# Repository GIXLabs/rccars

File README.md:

# Purpose

The following tutorial will get you up and running to build an RC car with the provided materials. All of the soldering is already done and the most of the code is flashed onto the brain board. It will be your responsibility to use the tools provided to you in your orientation bag along with the tools available in the Prototyping Lab to design and build a chassis for your car.

### Bill of Materials

# Electronics Assembly

1. Collect the above components from the Prototyping Lab staff.

1. Attach the components to the individual boards. AAA battery pack to brain board (only goes in one way). Bluetooth module to Bluetooth board (RCA, not RCM). Motors to motor board (needs a screwdriver and wires may need to be switched later).

1. Stack the boards together with the brain at the bottom and Bluetooth at the top. Make sure to align them properly (see image).

1. Try placing 3 AAA batteries in their holder and turn it on. If you've assembled everything correctly, the blue and red lights on the underside of the Bluetooth module should start blinking.

# Flashing Code

1. The code for the brain board is written in CircuitPython, which means you will not need to download any software to edit and manipulate the code. 
1. Download the RC Car code from [here](src/python/code.py). Make sure it is named `code.py`.

1. Using a micro USB cable, connect the brain board to your computer (you do not need to disconnect the other boards). Your computer should now have a new USB drive available named `CIRCUITPY` where the code is stored.
1. Click and drag `code.py` onto `CIRCUITPY`, replacing the file that is on the drive.
1. Your code should now be running on the brain board. If you would like to edit this code, just open `code.py` in any text editor (TextEdit and NotePad are fine). The new code will run whenever you save.
    1. Editing code this way does not give you access to any debugging outputs, so you may want to edit using [Mu](https://codewith.mu/en/download) or [Thonny](https://thonny.org/) so you can read any `print()` statements you add to the code.
    1. The max speed of the default code is slow, which you may want to change if you want to win the race.
    1. Python uses spacing in a particular way, so you may need to match the indendation of lines.
    1. For more details on how the code works see [here.](src/README.md)

# Connecting via Remote
1. Place the Bluetooth module marked `RCM` in the remote. It should only fit one way.

1. Plug in the 9V batteries on both your remote and turn on the AAA batteries on your car.

1. The lights on the Bluetooth dongles (HC-05) will stop blinking when they have successfully paired.

1. If it fails to pair, try power cycling the car ands the remote.

# Make your Chassis
1. Design and build the body of the RC car, you are welcome to use the materials provided in the Prototyping Lab from cardboard to wood. Make sure it holds everything! We've produced a tutorial if you'd like to start with a lasered template [here](lasering.md).

1. Attach the gear motors to the body of the RC car that you have designed/built and assemble the tires. Depending on how you attach the motors, you may have to change some wires to get it to move forward (instructions below).

# Debugging Motors
If you have been able to connect to your RC car, but it is going the wrong direction, you may need to swap the motor wires.
- If your car is going backward when it should be going forward - Swap the red and black wires on both motors.
- If your car is going left when it should be going right or right when it should be going left - Swap which side of the motor driver your motors are wired to.
- For other problems, ask a member of the Prototyping Lab staff.

### Congratulations you are now connected to the RC car! Happy racing! 🏁🏎

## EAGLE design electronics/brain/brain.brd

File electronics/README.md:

# Purpose
This is where any information about the electronics will go. The Eagle files (.sch and .brd) will be in a subdirectory).

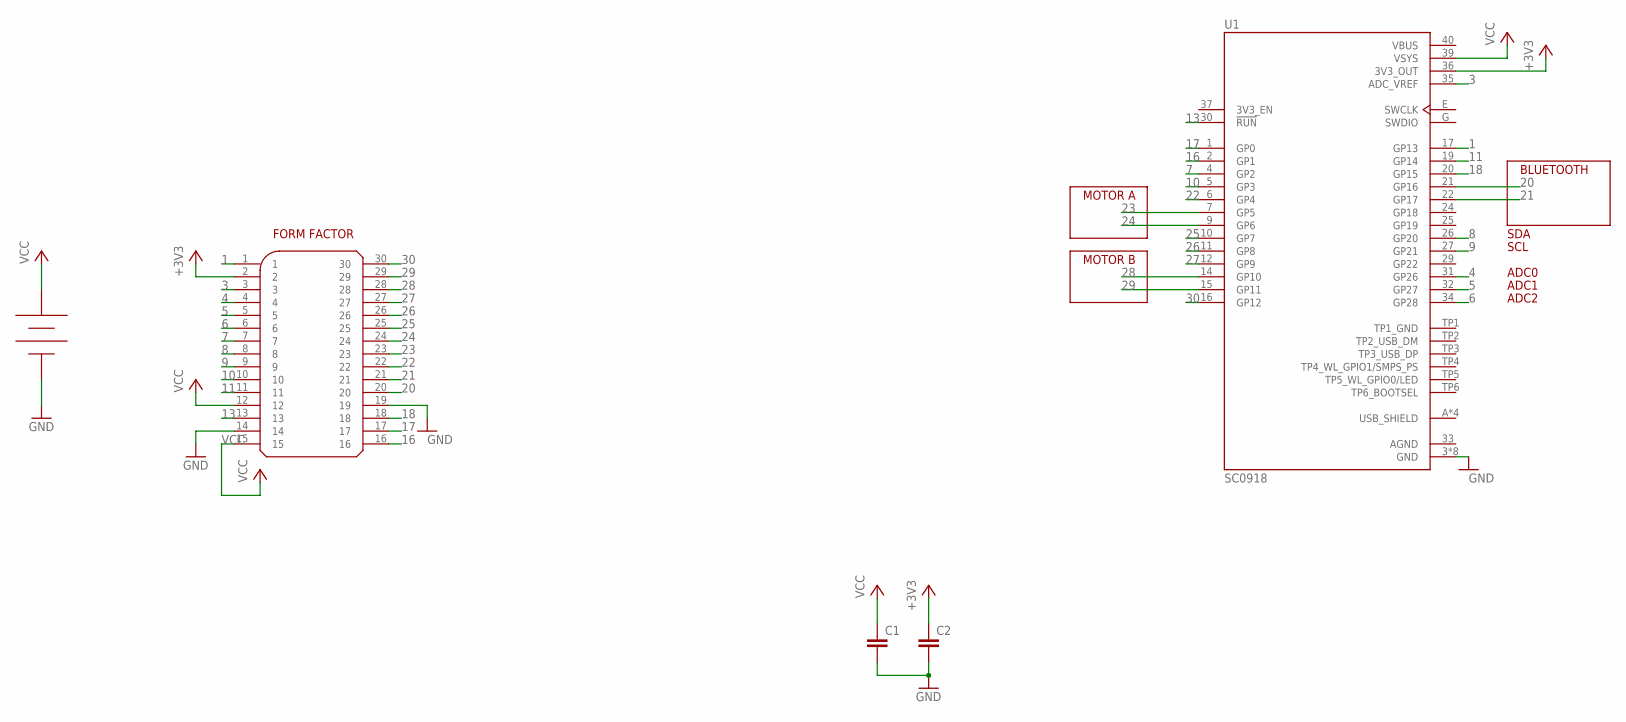
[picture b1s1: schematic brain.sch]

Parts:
C1, C2: C-EU050-025X075; C050-025X075
U1: SC0918; MODULE_SC0918
U$4: RC_FORM_FACTOR
U$6: LIPO_BATTERY; JST_PH

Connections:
1: U1.17 (GP13), U$4.1
3: U1.35 (ADC_VREF), U$4.3
4: U1.31 (GP26), U$4.4
5: U1.32 (GP27), U$4.5
6: U1.34 (GP28), U$4.6
7: U1.4 (GP2), U$4.7
8: U1.26 (GP20), U$4.8
9: U1.27 (GP21), U$4.9
10: U1.5 (GP3), U$4.10
11: U1.19 (GP14), U$4.11
13: U1.30 (!RUN), U$4.13
16: U1.2 (GP1), U$4.16
17: U1.1 (GP0), U$4.17
18: U1.20 (GP15), U$4.18
20: U1.21 (GP16), U$4.20
21: U1.22 (GP17), U$4.21
22: U1.6 (GP4), U$4.22
23: U1.7 (GP5), U$4.23
24: U1.9 (GP6), U$4.24
25: U1.10 (GP7), U$4.25
26: U1.11 (GP8), U$4.26
27: U1.12 (GP9), U$4.27
28: U1.14 (GP10), U$4.28
29: U1.15 (GP11), U$4.29
30: U1.16 (GP12), U$4.30
+3V3: C2.1, U1.36 (3V3_OUT), U$4.2
AGND: U1.33 (AGND)
GND: C1.2, C2.2, U1.3 (GND), U1.8 (GND), U1.13 (GND), U1.18 (GND), U1.23 (GND), U1.28 (GND), U1.38 (GND), U1.F (GND), U$4.14, U$4.19, U$6.GND (NEG)
TP1_GND: U1.TP1 (TP1_GND)
USB_SHIELD: U1.A (USB_SHIELD), U1.B (USB_SHIELD), U1.C (USB_SHIELD), U1.D (USB_SHIELD)
VBUS: U1.40 (VBUS)
VCC: C1.1, U1.39 (VSYS), U$4.12, U$4.15, U$6.POS

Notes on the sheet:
FORM FACTOR
ADC0
ADC1
ADC2
MOTOR A
MOTOR B
BLUETOOTH
SDA
SCL

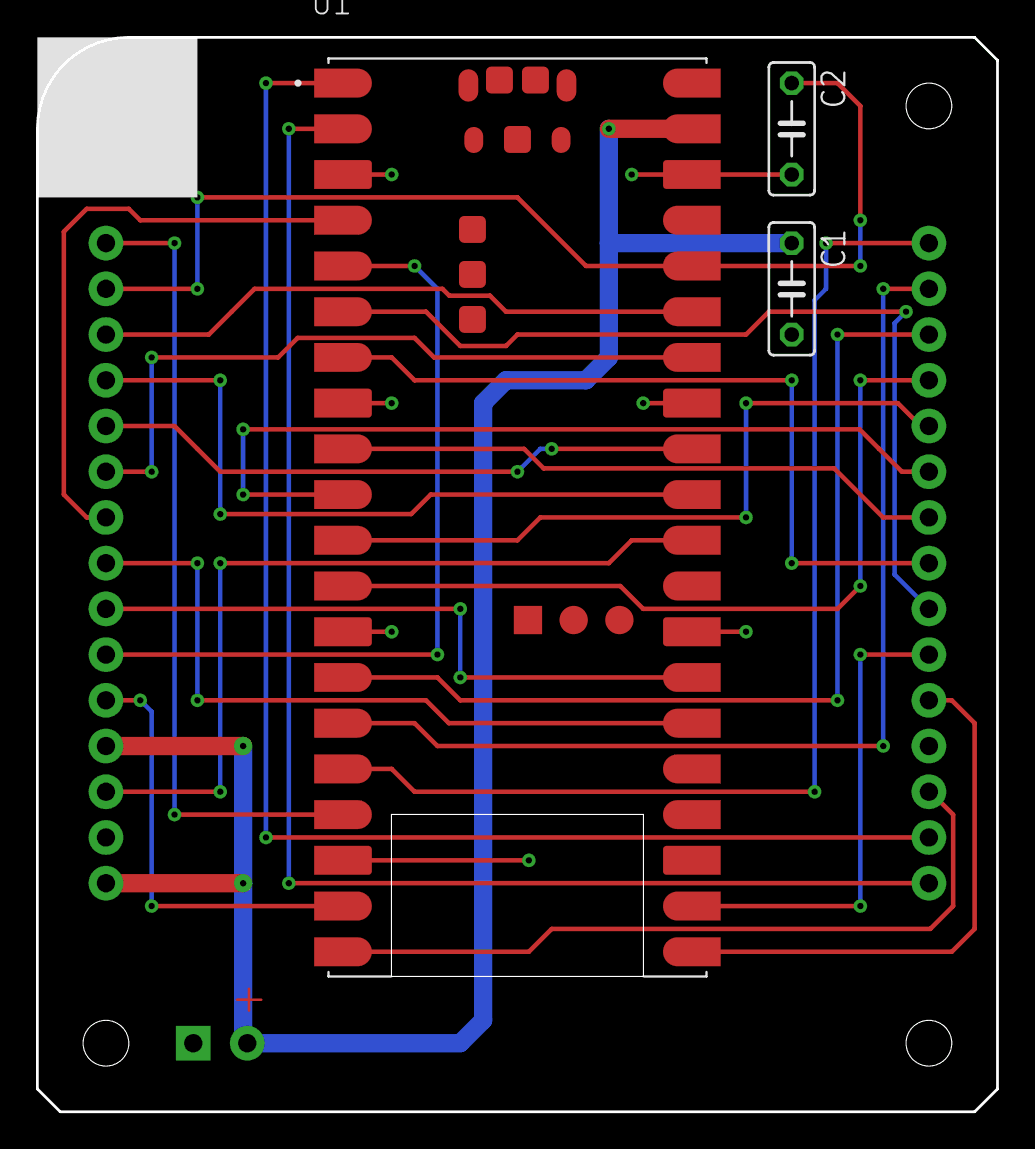
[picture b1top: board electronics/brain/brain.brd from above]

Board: 2 copper layers, 53.3 x 59.7 mm, 5 parts (0 on the bottom side), 29 nets.

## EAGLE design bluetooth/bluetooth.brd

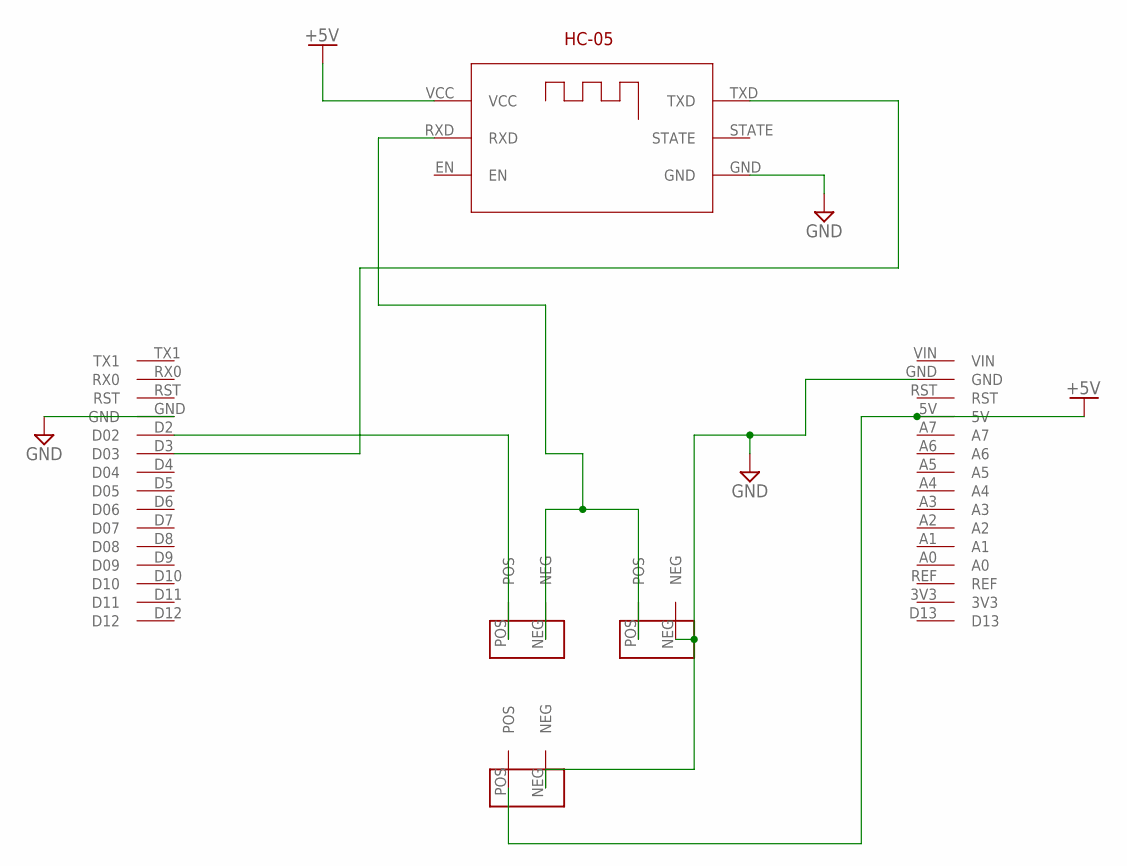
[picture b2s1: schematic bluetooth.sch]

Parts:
POWER: CAP
U$1: ARDUINO-NANO-JUMPER-1
U$2: ARDUINO-NANO-JUMPER-2
U$3, U$4: RESISTOR
U$5: HC-05

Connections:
+5V: POWER.POS, U$2.5V, U$5.VCC
D02: U$1.D2 (D02), U$3.POS
D03: U$1.D3 (D03), U$5.TXD
GND: POWER.NEG, U$1.GND, U$2.GND, U$4.NEG, U$5.GND
RX: U$3.NEG, U$4.POS, U$5.RXD

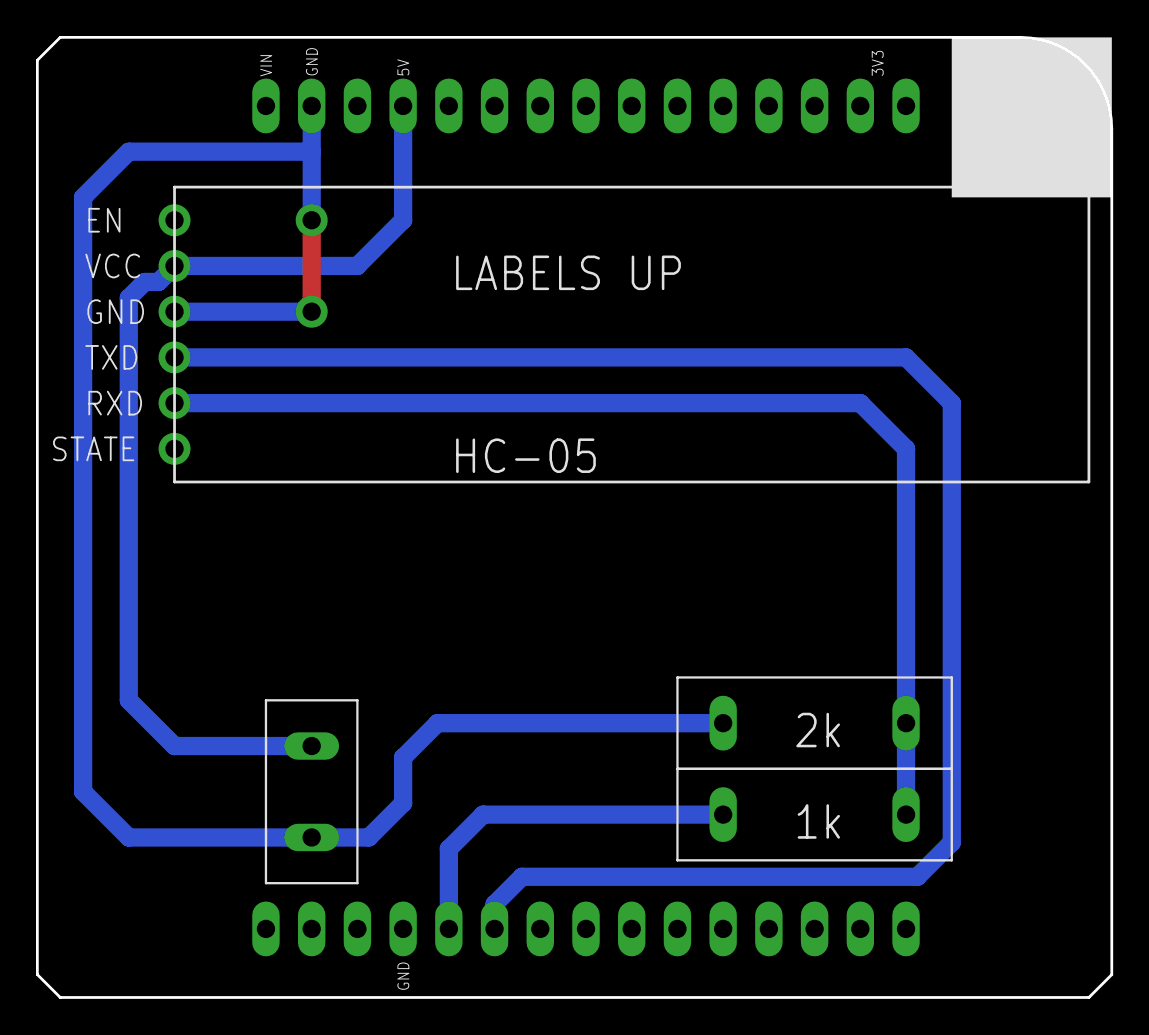
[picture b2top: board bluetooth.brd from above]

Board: 2 copper layers, 59.7 x 53.3 mm, 6 parts (0 on the bottom side), 5 nets.

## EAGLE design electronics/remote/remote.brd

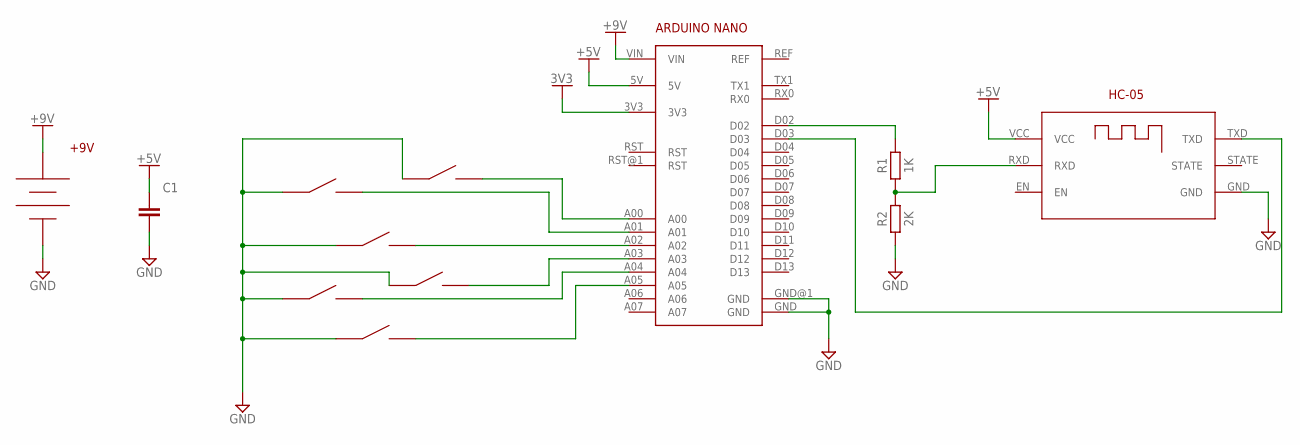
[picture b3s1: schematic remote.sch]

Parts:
C1: C_RADIAL-12.5MM-DIA; CAPRD550W60D1025H1250B
DOWN: TACT_SWITCH_6MM
LEFT: TACT_SWITCH_6MM
LEFT_BUMPER: TACT_SWITCH_6MM
R1: 1K; RESAD1176W63L850D250B
R2: 2K; RESAD1176W63L850D250B
RIGHT: TACT_SWITCH_6MM
RIGHT_BUMPER: TACT_SWITCH_6MM
U$1: 9V_BATTERY
U$2: HC-05
U$9: ARDUINO-NANO-V3
UP: TACT_SWITCH_6MM

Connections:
3V3: U$9.3V3
+5V: C1.1, U$2.VCC, U$9.5V
+9V: U$1.POS (9V), U$9.VIN
GND: C1.2, DOWN.A1 (A), DOWN.A2 (A), LEFT.A1 (A), LEFT.A2 (A), LEFT_BUMPER.A1 (A), LEFT_BUMPER.A2 (A), R2.1, RIGHT.A1 (A), RIGHT.A2 (A), RIGHT_BUMPER.A1 (A), RIGHT_BUMPER.A2 (A), U$1.NEG, U$2.GND, U$9.GND, U$9.GND@1 (GND), UP.A1 (A), UP.A2 (A)
unnamed: R1.2, U$9.D02
unnamed: RIGHT_BUMPER.B1 (B), RIGHT_BUMPER.B2 (B), U$9.A00
unnamed: LEFT_BUMPER.B1 (B), LEFT_BUMPER.B2 (B), U$9.A01
unnamed: U$9.A02, UP.B1 (B), UP.B2 (B)
unnamed: RIGHT.B1 (B), RIGHT.B2 (B), U$9.A03
unnamed: LEFT.B1 (B), LEFT.B2 (B), U$9.A04
unnamed: DOWN.B1 (B), DOWN.B2 (B), U$9.A05
unnamed: R1.1, R2.2, U$2.RXD
unnamed: U$2.TXD, U$9.D03

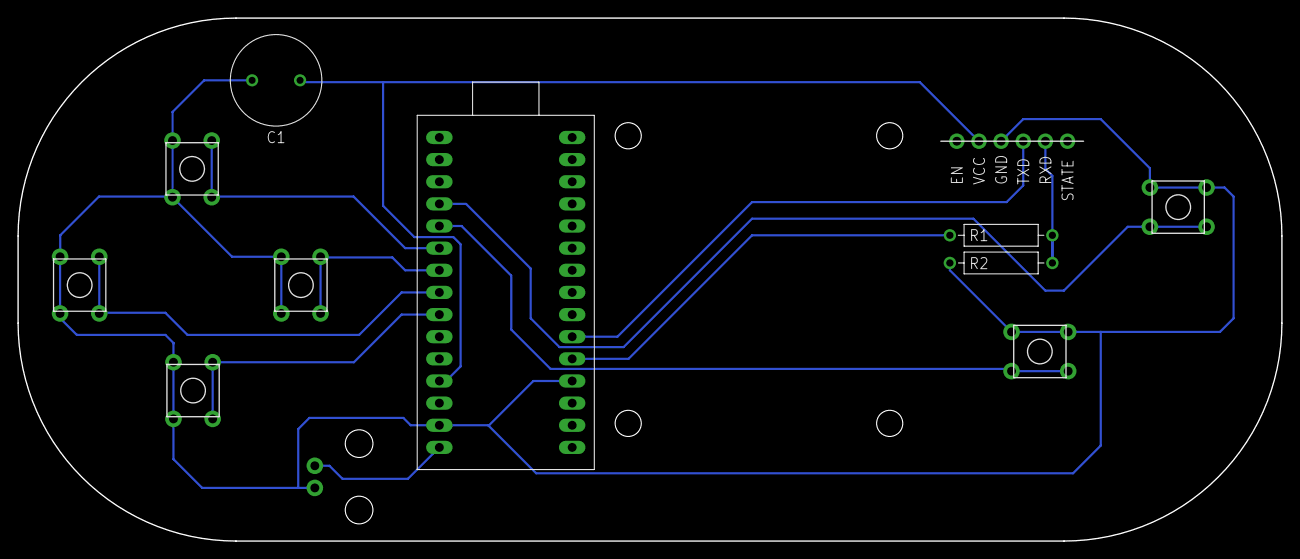
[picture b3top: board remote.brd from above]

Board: 2 copper layers, 145.0 x 60.0 mm, 12 parts (1 on the bottom side), 12 nets.

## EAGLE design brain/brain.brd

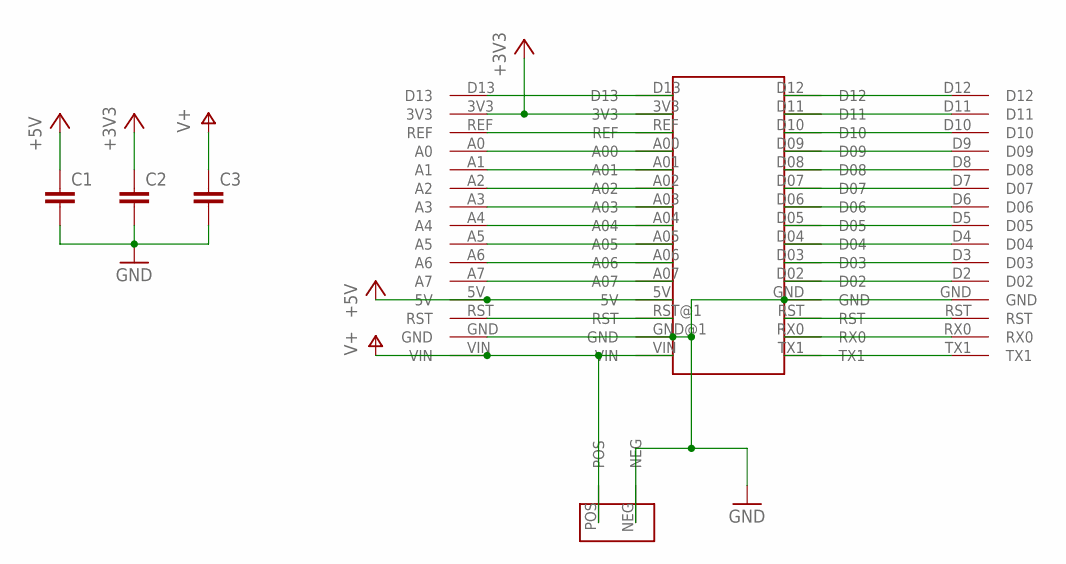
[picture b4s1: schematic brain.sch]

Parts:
C1, C2, C3: C-EU050-025X075; C050-025X075
U$1: ARDUINO-NANO-V3
U$2: ARDUINO-NANO-JUMPER-1
U$3: POWER-IN
U$5: ARDUINO-NANO-JUMPER-2

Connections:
+3V3: C2.1, U$1.3V3, U$5.3V3
+5V: C1.1, U$1.5V, U$5.5V
A00: U$1.A00, U$5.A0
A01: U$1.A01, U$5.A1
A02: U$1.A02, U$5.A2
A03: U$1.A03, U$5.A3
A04: U$1.A04, U$5.A4
A05: U$1.A05, U$5.A5
A06: U$1.A06, U$5.A6
A07: U$1.A07, U$5.A7
D02: U$1.D02, U$2.D2 (D02)
D03: U$1.D03, U$2.D3 (D03)
D04: U$1.D04, U$2.D4 (D04)
D05: U$1.D05, U$2.D5 (D05)
D06: U$1.D06, U$2.D6 (D06)
D07: U$1.D07, U$2.D7 (D07)
D08: U$1.D08, U$2.D8 (D08)
D09: U$1.D09, U$2.D9 (D09)
D10: U$1.D10, U$2.D10
D11: U$1.D11, U$2.D11
D12: U$1.D12, U$2.D12
D13: U$1.D13, U$5.D13
GND: C1.2, C2.2, C3.2, U$1.GND, U$1.GND@1 (GND), U$2.GND, U$3.NEG, U$5.GND
REF: U$1.REF, U$5.REF
RST: U$1.RST, U$1.RST@1 (RST), U$2.RST, U$5.RST
RX0: U$1.RX0, U$2.RX0
TX1: U$1.TX1, U$2.TX1
V+: C3.1, U$1.VIN, U$3.POS, U$5.VIN

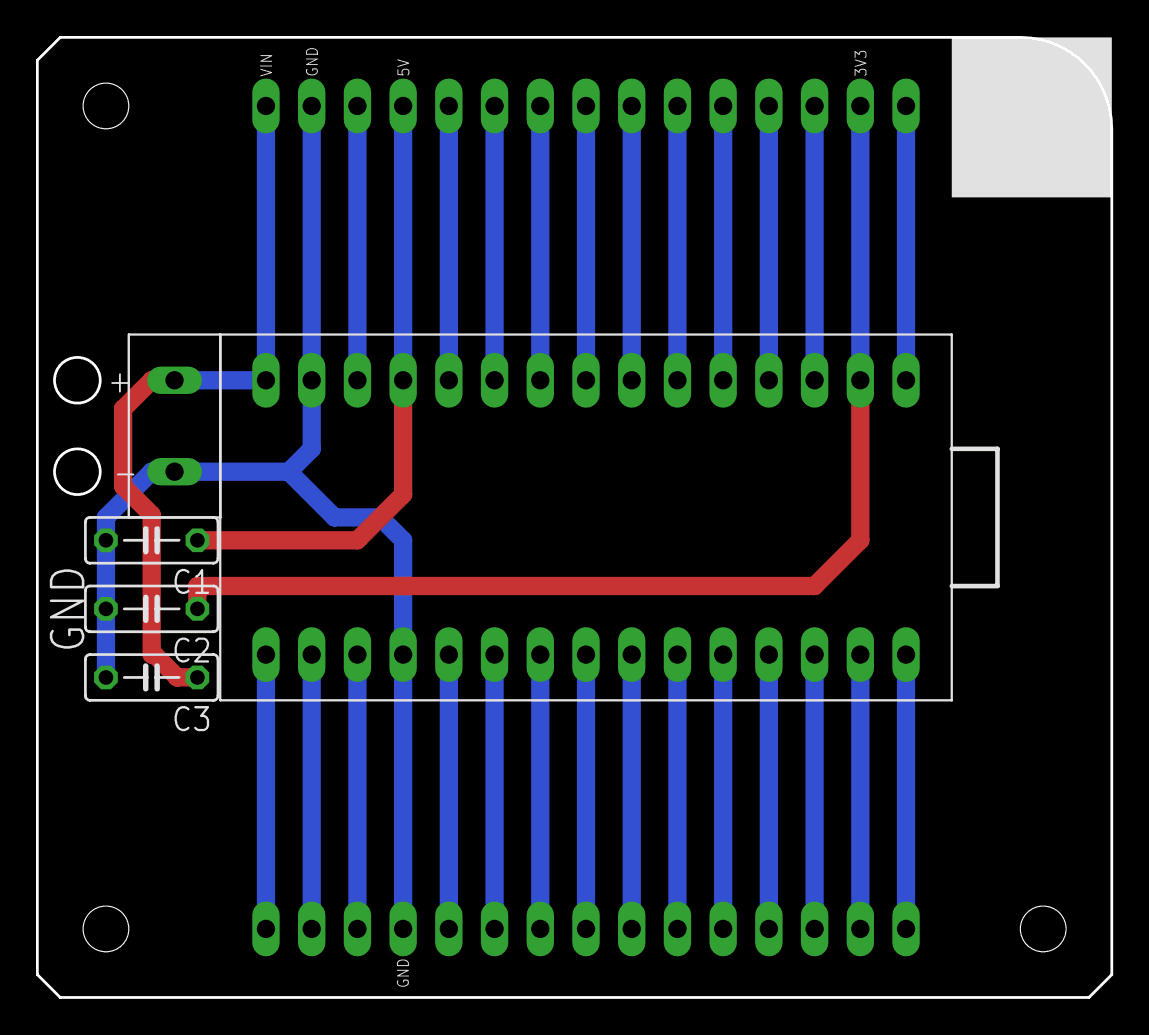
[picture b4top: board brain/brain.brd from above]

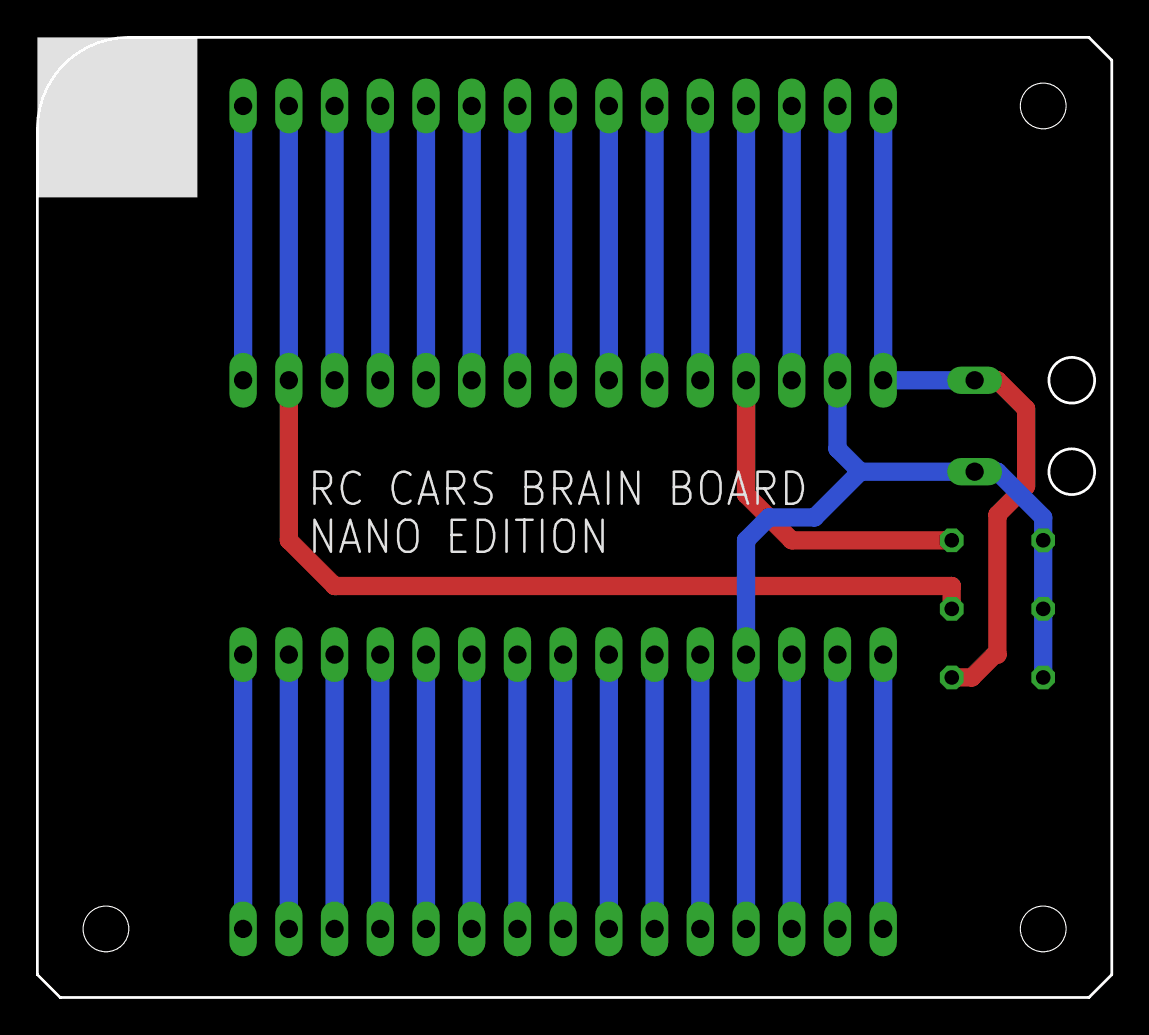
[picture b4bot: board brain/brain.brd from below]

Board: 2 copper layers, 59.7 x 53.3 mm, 7 parts (2 on the bottom side), 28 nets.

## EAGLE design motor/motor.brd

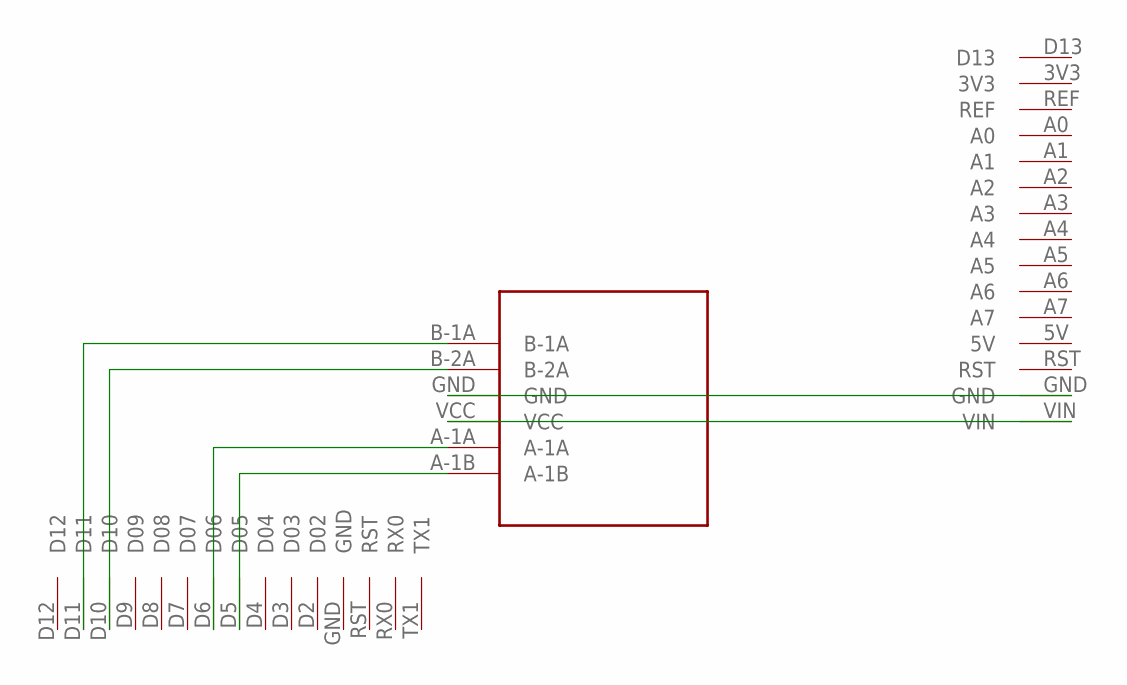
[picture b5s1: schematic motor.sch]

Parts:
U$1: ARDUINO-NANO-JUMPER-1
U$2: L9110S; L9100S
U$7: ARDUINO-NANO-JUMPER-2

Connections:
D05: U$1.D5 (D05), U$2.A-1B
D06: U$1.D6 (D06), U$2.A-1A
unnamed: U$2.GND, U$7.GND
unnamed: U$2.VCC, U$7.VIN
unnamed: U$1.D11, U$2.B-1A
unnamed: U$1.D10, U$2.B-2A

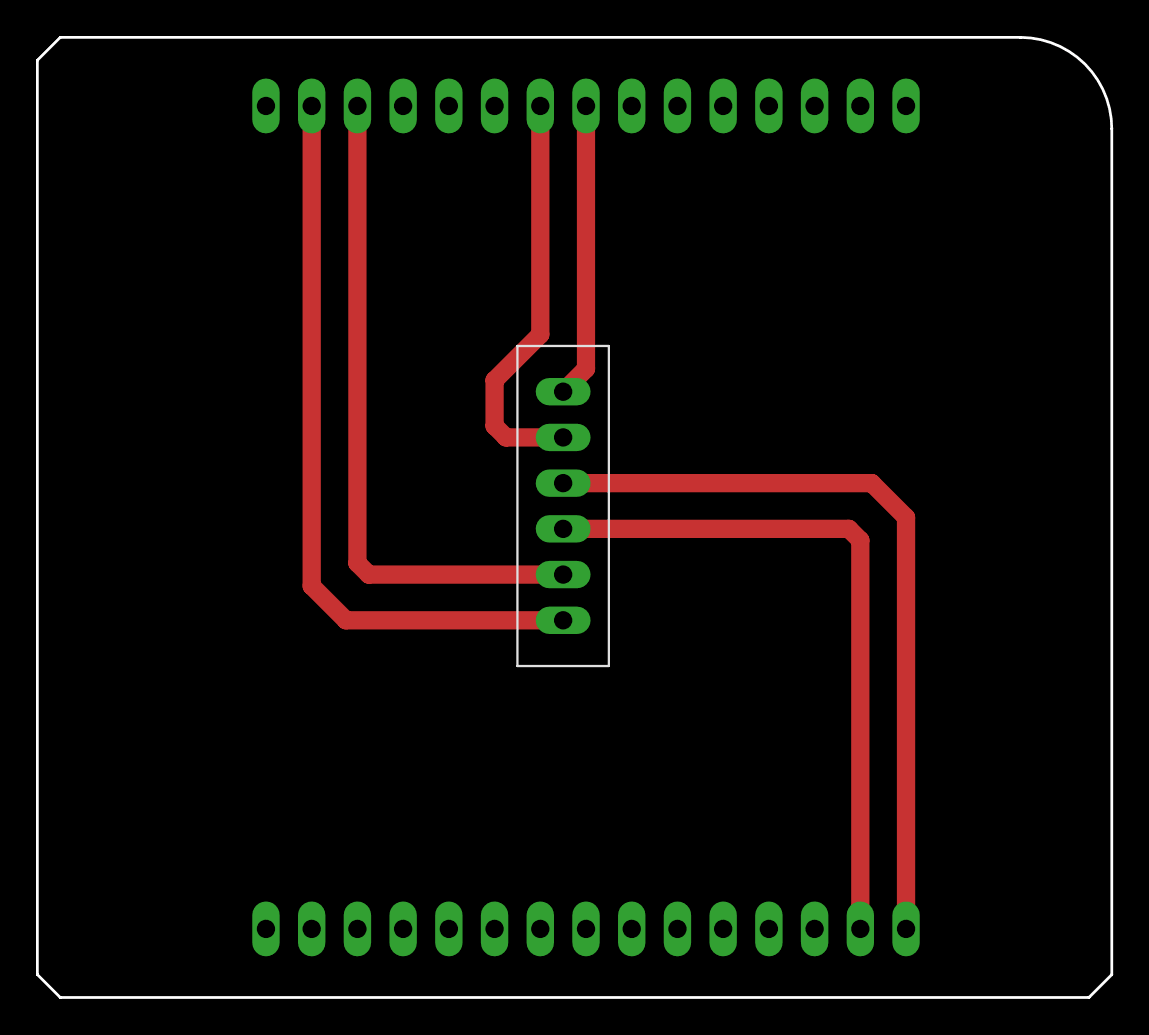
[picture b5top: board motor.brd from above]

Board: 2 copper layers, 59.7 x 53.3 mm, 3 parts (0 on the bottom side), 6 nets.

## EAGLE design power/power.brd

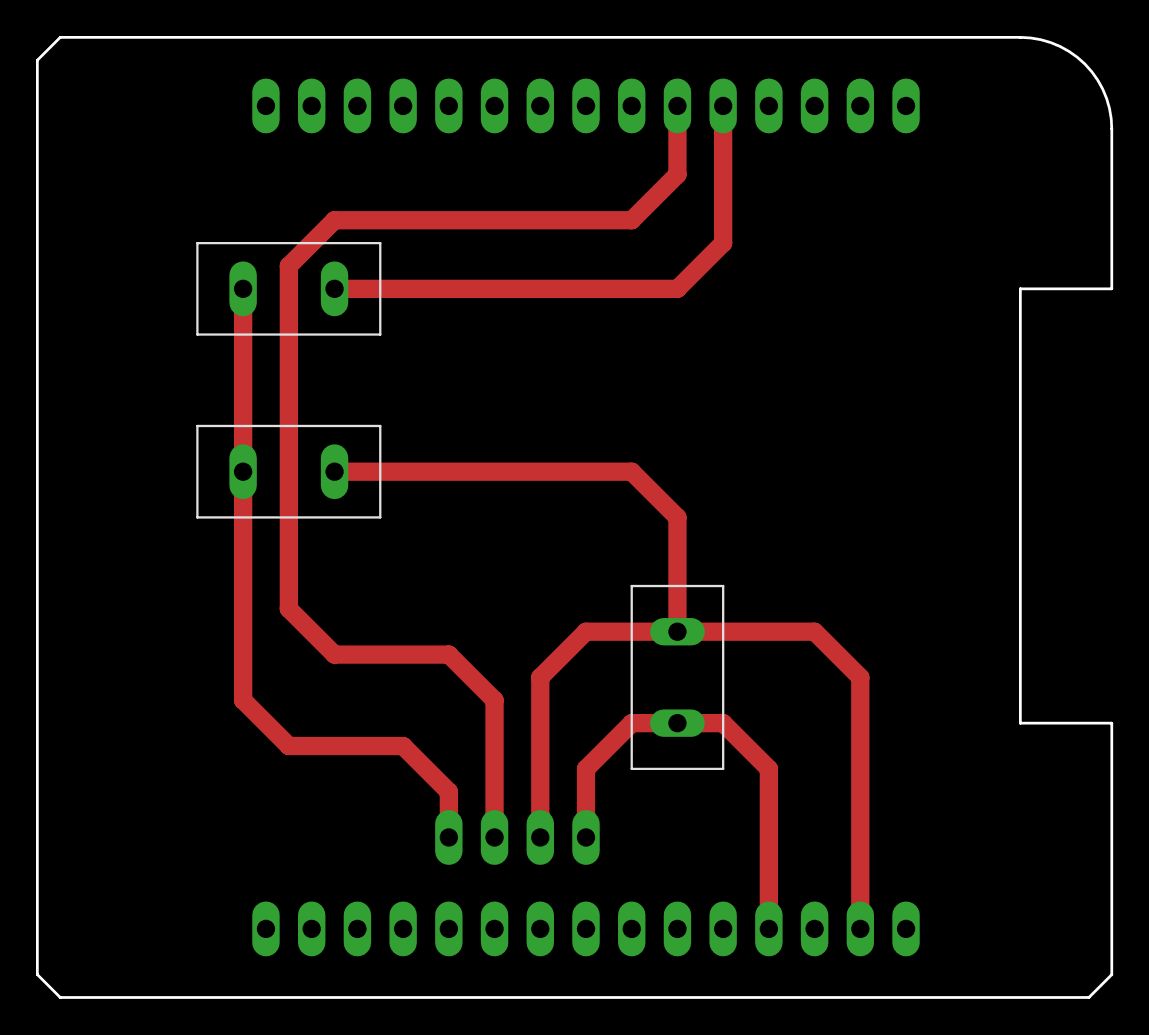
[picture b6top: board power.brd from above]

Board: 2 copper layers, 59.7 x 53.3 mm, 6 parts (0 on the bottom side), 5 nets.

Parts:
POWER: CAP
U$1: ARDUINO-NANO-JUMPER-1
U$2: ARDUINO-NANO-JUMPER-2
U$3, U$4: RESISTOR
U$6: BT

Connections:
5V: POWER.POS, U$2.5V, U$6.VCC
D02: U$1.D2, U$3.POS
D03: U$1.D3, U$6.TXD
GND: POWER.NEG, U$2.GND, U$4.NEG, U$6.GND
RX: U$3.NEG, U$4.POS, U$6.RXD

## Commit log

2022-06-22 Added some directories to structure the information.
2022-06-22 Fixed my own dumb directory mistakes.
2022-06-24 arduino code and stl files added
2022-06-24 comments for arduino app added, double and trile spaces removed
2022-07-05 new STL files
2022-07-15 initial working src code
2022-07-21 fusion tyre mold added
2022-08-04 renamed stuff added gitignore
2022-08-09 added arduino code to help change hc05 module to command mode
2022-08-09 added documentation to switch to command mode
2022-08-16 updated documentation for HC-05
2022-08-16 updated code for the proper RX and TX pins
2022-08-16 Adding Garrett's files. Appears to be missing the Bluetooth board.
2022-08-17 Test change
2022-08-17 I clearly need sleep
2022-08-17 Added chamfers and filet to brain board.
2022-08-17 Added chamfers and filet to remaining boards.
2022-08-17 Added decoupling capacitors to brain board. Also adjusted the origin to be in the bottom left corner of the PCB.
2022-08-17 Added mini USB notch on brain board to aid in placing Nano.
2022-08-19 Moved all boards so their bottom left corners are at the origin.
2022-08-19 Fixed board lengths for motor and power boards.
2022-08-20 adding library file
2022-08-22 Minor filename changes for easier use of command line.
2022-08-22 On brain board: Added holes for strain relief of power cables. Added silkscreen to indicate ground and different power pins on Nano. Added silkscreen denoting the board. Added silkscreen to mark posi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
2022-08-23 Changed name of power board to bluetooth to reflect its new purpose.
2022-08-23 Update RC_car_code.ino
    Changed Serial Comm pins to reflect hardware configuration
2022-08-26 Update RC_car_code.ino
    Swapped Motor B pins to simplify wire routing
2022-08-26 Updated Boards for New Configuration
    Bluetooth board has been rearranged to accommodate board slot-in
    Motor Control Board flipped to be in the right spot
2022-08-29 arduino code for master and apprentice
2022-08-30 update name
2022-08-30 update foldername
2022-08-30 Added breadboard board. This commit is going to production.
2022-09-01 newcommitmessage
2022-09-02 WiP tutorial
2022-09-06 finaldrafttutorial
2022-09-07 made changes to the readme.md
2022-09-07 made minor changes
2022-09-08 master apprentice single script initial commit
2022-09-08 Master-appren unified code, cosmetic changes
2022-09-09 Moved PCBs files into this repository. Old rccars_pcb is now deprecated.
2022-09-10 Just checking how images look in main tutorial
2022-09-12 fixed the issues
2022-09-13 not working yet
2022-09-14 Setup the speed as a variable at the top of the script. Also changed the name of the stop command to not conflict with reserved term.
2022-09-14 Removed duplicate board designs. Duplication due to Kevin's lack of communication.
2022-09-15 Simplified some of the language on the instructions. Added some motor debugging.
2022-09-15 still need testing
2022-09-15 added tyre motor mount.
2022-09-15 still need testing and clean up code
2022-09-15 put the apprentice to original code
2022-09-15 unified code cleanup
2022-09-15 Initial commit of remote code. Bumper buttons currently send forward character, but that should be changed to handle other characters.
2022-09-15 name change for rccar
2022-09-15 minor
2022-09-15 Added stop command to remote code.
2022-09-15 change baudrate
2022-09-15 moved all unused hc-05 code to one folder
2022-09-15 changed baud rate
2022-09-15 hc-05 unified code cleanup
2022-09-15 updated flash code tutorial
2022-09-16 added the default password for the HC-05
2022-09-16 clean up the folder
2022-09-16 this file is not neccessary
2022-09-19 Added some raw graphics for showing the components in the tutorial
2022-09-21 Added new graphics for bill of materials section.
2022-09-22 Made some edits to tutorial to clarify Bluetooth connectivity.
2022-09-22 Removed redundancy library file.
2023-08-03 Added initial notes and motor test script for CircuitPython conversion
2023-08-03 Mapped out all of the pins to the form factor on the current Nano brain board. These will inform the pin mapping on the Pico.
2023-08-03 Added form factor part to library to make it easier to build new boards to stack.
2023-08-04 Updated motor pins. Added Bluetooth test script.
2023-08-05 Fleshed out pin mapping. Routed new brain board.
2023-08-07 This version was ordered.
2023-08-15 Fixed power issue in current iteration of boards.
2023-08-17 Added pwm to both motors.
2023-08-17 Added initial bit of main script, with framework for motor class.
2023-08-17 Added some Bluetooth connection with motors, just forward and stop. Still need all other directions.
2023-08-17 Code is working for all directions and could be used now. Still needs edits to add boost and improve editability. Shooting for less than 20 lines of code in the main document with motor and bluetooth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
2023-08-17 Removed fragment on border. Changed vias on VCC to same diameter as traces (40 mil).
2023-08-17 Added different codes for the extra buttons.
2023-08-22 Split motor controls into a separte file. Added if statements for other inputs. Pseudocode for boost.
2023-08-22 Added boost functionality. Changed a few variable names for readability.
2023-08-22 Updated some of the tutorial content to reflect the change to CircuitPython.
2023-08-22 Removed old brain code and earlier versions of HC_05 pairing code.
2023-09-05 Added picture for downloading code.
2023-09-05 Added different assets to the tutorial and changed the wording.
2023-09-05 Moved chassis making to later in the instructions.
2023-09-15 Added new image showing all components laid out.
2023-09-15 Changed layout image target in README.md
2023-09-15 Added button layout and theory of operation for code.
2023-09-15 Added links to theory of operation from main page.
2023-09-15 Fixed erroneous numbers on boost speed in Theory of Operation.
2023-09-15 Cleaned up a lot of old assets that were no longer needed.
2023-09-21 Removed several unneeded files.
2023-09-21 Added two bases for cars.
2023-09-22 Added link to svgs. Added line about attaching the Bluetooth to the remote.
2024-09-04 Started port of laser tutorial from input challenge.
2024-09-04 Copied over assets for lasering tutorial from InputChallenge.
2024-09-04 Updated links to assets in lasering tutorial.
2024-09-04 Added link to lasering tutorial in main README.
2024-09-04 Updated svg folder with new design folders
2024-09-05 Added link to Aayush's car.
2024-09-05 Added laser safety to lasering tutorial.
2024-09-05 Updated links to lasering tutorial. Fixed one instance of Labs vs Lab
2024-09-07 Add RC_Car_Van folder with files
2024-09-19 Added batperson car.
2024-09-19 Updated links to templates in lasering document.
2024-09-19 Fixed typo.
2025-06-26 Update prompt device name input and more
